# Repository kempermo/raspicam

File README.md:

# raspiCAM

### Setup WiFi
In order to setup WiFi with the correct credentials open the attached file "wpa_supplicant.conf" with a text editor and fill in the correct ssid and password that matches your WiFi setup.

Insert the sd-card from raspi into your computer and open it in the finder. Place the generated "wpa_supplicant.conf" onto the card.

Insert the card back to the raspi and boot. The raspi should now boot and connect to the new WiFi.

### Helpful applications
LanScan for getting the IP address of the raspi - https://apps.apple.com/de/app/lanscan/id472226235?mt=12

### Credetials for login through ssh
User: pi
Passwort: user

### Terminal command for initializing the ssh connection
ssh pi@192.168.20.248 (replace with the proper IP address of your raspi)

### Helpful terminal commands
ls - List current directory contents
cd + ... - entering a directory
cd .. - going back one directory
sudo nano + ... - opening a file in editor
sudo python3 + ... - running a python script with python3
ps aux - list current running processes
sudo kill 425 - kill the process with ID 425

### Helpful key commands
"option"+"c" - quit the current running process

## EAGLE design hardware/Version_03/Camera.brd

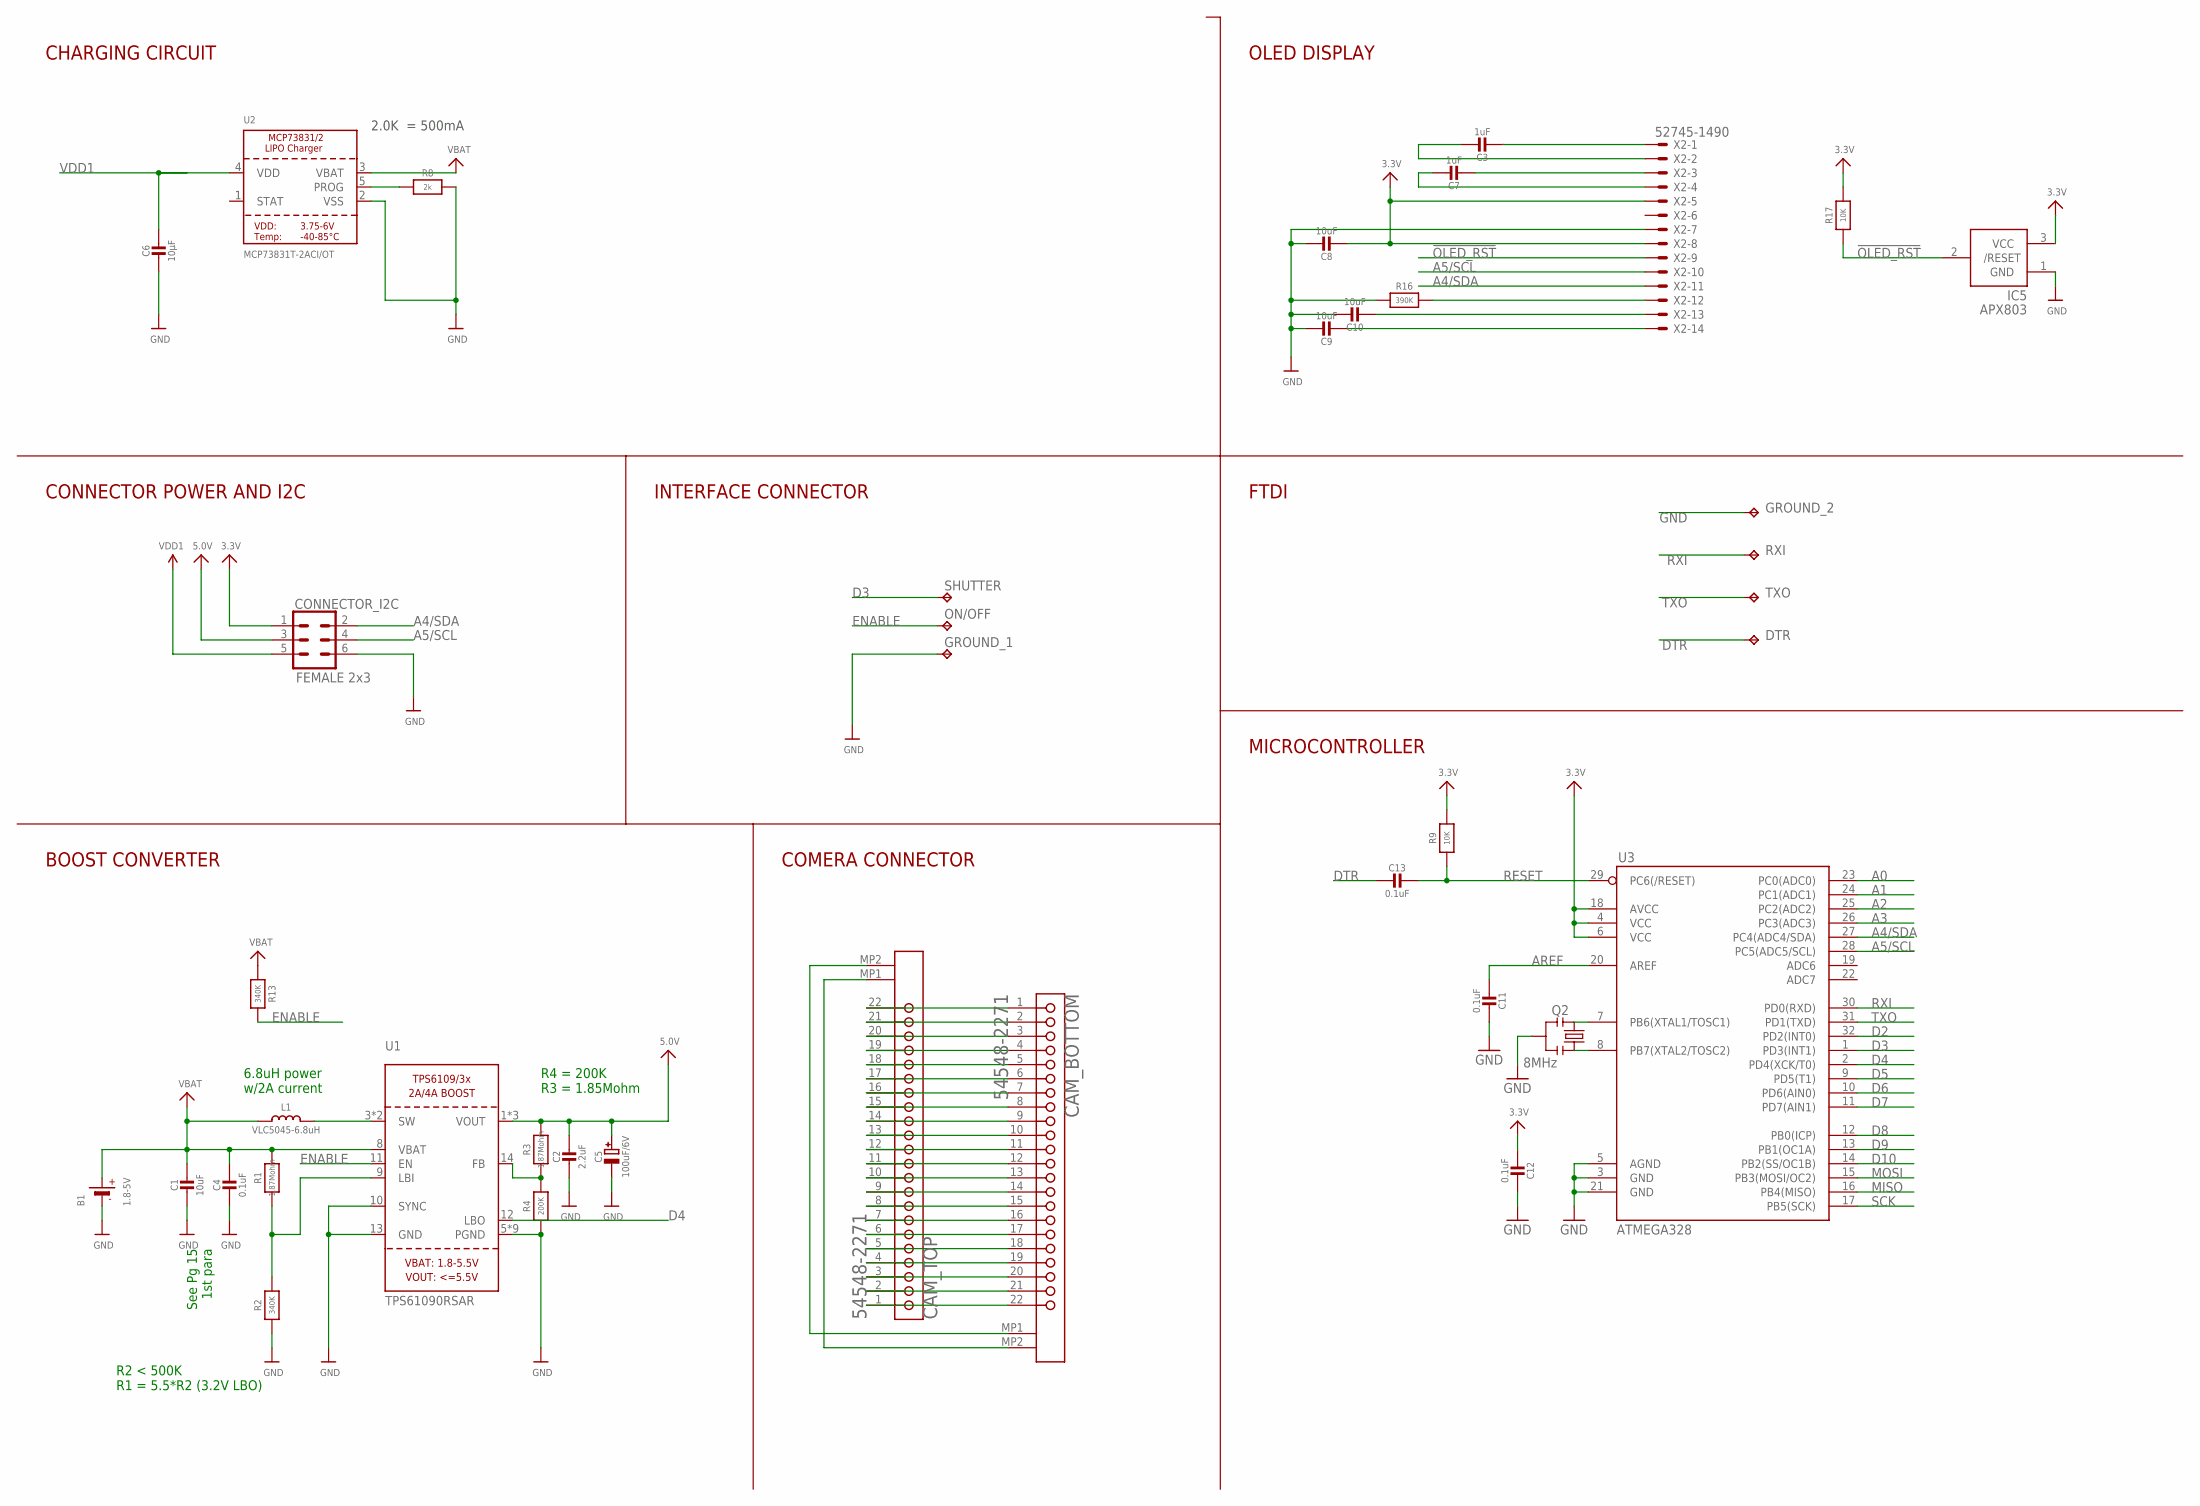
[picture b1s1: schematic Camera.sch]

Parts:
B1: 1.8-5V; JSTPH2
C1, C8, C9, C10: 10uF; 0805-NO
C2: 2.2uF; 0805-NO
C3, C7: 1uF; 0805-NO
C4, C11, C12, C13: 0.1uF; 0805-NO
C5: 100uF/6V; EIA3528-21/B-R
C6: 10µF; 0805-NO
CAM_BOTTOM: MOLEX_54548-2271MOLEX_54548-2271_0_0; MOLEX_54548-2271_0
CAM_TOP: MOLEX_54548-2271MOLEX_54548-2271_0_0; MOLEX_54548-2271_0
CONNECTOR_I2C: FEMALE 2x3; 2X3
DTR: TPB1,27; B1,27
GROUND_1, GROUND_2: TPB1,27; B1,27
IC5: APX803; SOT23
L1: VLC5045-6.8uH; INDUCTOR_5X5MM_TDK_VLC5045
ON/OFF: TPB1,27; B1,27
Q2: 8MHz; RESONATOR-SMD
R1, R3: 1.87Mohm; 0805-NO
R2, R13: 340K; 0805-NO
R4: 200K; 0805-NO
R8: 2k; 0805-NO
R9, R17: 10K; 0805-NO
R16: 390K; 0805-NO
RXI: TPB1,27; B1,27
SHUTTER: TPB1,27; B1,27
TXO: TPB1,27; B1,27
U1: TPS61090RSAR; PVQFN-16
U2: MCP73831T-2ACI/OT; SOT23-5
U3: ATMEGA328; TQFP32-08
X2: 52745-1490

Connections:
3.3V: C8.2, C12.2, CONNECTOR_I2C.1, IC5.3 (VCC), R9.2, R17.2, U3.4 (VCC), U3.6 (VCC), U3.18 (AVCC), X2.5, X2.8
5.0V: C2.1, C5.+, CONNECTOR_I2C.3, R3.2, U1.1 (VOUT), U1.15 (VOUT), U1.16 (VOUT)
!OLED_RST: IC5.2 (/RESET), R17.1, X2.9
A0: U3.23 (PC0(ADC0))
A1: U3.24 (PC1(ADC1))
A2: U3.25 (PC2(ADC2))
A3: U3.26 (PC3(ADC3))
A4/SDA: CONNECTOR_I2C.2, U3.27 (PC4(ADC4/SDA)), X2.11
A5/SCL: CONNECTOR_I2C.4, U3.28 (PC5(ADC5/SCL)), X2.10
AREF: C11.2, U3.20 (AREF)
D2: U3.32 (PD2(INT0))
D3: SHUTTER.TP, U3.1 (PD3(INT1))
D4: U1.12 (LBO), U3.2 (PD4(XCK/T0))
D5: U3.9 (PD5(T1))
D6: U3.10 (PD6(AIN0))
D7: U3.11 (PD7(AIN1))
D8: U3.12 (PB0(ICP))
D9: U3.13 (PB1(OC1A))
D10: U3.14 (PB2(SS/OC1B))
DTR: C13.2, DTR.TP
ENABLE: ON/OFF.TP, R13.2, U1.11 (EN)
GND: B1.1 (-), C1.2, C2.2, C4.2, C5.-, C6.2, C8.1, C9.1, C10.1, C11.1, C12.1, CONNECTOR_I2C.6, GROUND_1.TP, GROUND_2.TP, IC5.1 (GND), Q2.2, R2.1, R4.1, R8.2, R16.1, U1.5 (PGND), U1.6 (PGND), U1.7 (PGND), U1.10 (SYNC), U1.13 (GND), U1.P$18 (PGND), U1.P$19 (PGND), U1.P$20 (PGND), U1.P$21 (PGND), U1.P$22 (PGND), U1.THERMAL (PGND), U2.2 (VSS), U3.3 (GND), U3.5 (AGND), U3.21 (GND), X2.7
MISO: U3.16 (PB4(MISO))
MOSI: U3.15 (PB3(MOSI/OC2))
unnamed: L1.P$2 (2), U1.3 (SW), U1.4 (SW)
unnamed: CAM_BOTTOM.MP1, CAM_TOP.MP2
unnamed: R1.1, R2.2, U1.9 (LBI)
unnamed: CAM_BOTTOM.MP2, CAM_TOP.MP1
unnamed: R3.1, R4.2, U1.14 (FB)
unnamed: CAM_BOTTOM.1, CAM_TOP.22
unnamed: CAM_BOTTOM.2, CAM_TOP.21
unnamed: R8.1, U2.5 (PROG)
unnamed: CAM_BOTTOM.3, CAM_TOP.20
unnamed: CAM_BOTTOM.4, CAM_TOP.19
unnamed: C3.2, X2.1
unnamed: C3.1, X2.2
unnamed: C7.2, X2.3
unnamed: C7.1, X2.4
unnamed: C10.2, X2.13
unnamed: R16.2, X2.12
unnamed: C9.2, X2.14
unnamed: Q2.1, U3.8 (PB7(XTAL2/TOSC2))
unnamed: Q2.3, U3.7 (PB6(XTAL1/TOSC1))
unnamed: CAM_BOTTOM.5, CAM_TOP.18
unnamed: CAM_BOTTOM.6, CAM_TOP.17
unnamed: CAM_BOTTOM.7, CAM_TOP.16
unnamed: CAM_BOTTOM.8, CAM_TOP.15
unnamed: CAM_BOTTOM.9, CAM_TOP.14
unnamed: CAM_BOTTOM.10, CAM_TOP.13
unnamed: CAM_BOTTOM.11, CAM_TOP.12
unnamed: CAM_BOTTOM.12, CAM_TOP.11
unnamed: CAM_BOTTOM.13, CAM_TOP.10
unnamed: CAM_BOTTOM.14, CAM_TOP.9
unnamed: CAM_BOTTOM.15, CAM_TOP.8
unnamed: CAM_BOTTOM.16, CAM_TOP.7
unnamed: CAM_BOTTOM.17, CAM_TOP.6
unnamed: CAM_BOTTOM.18, CAM_TOP.5
unnamed: CAM_BOTTOM.19, CAM_TOP.4
unnamed: CAM_BOTTOM.20, CAM_TOP.3
unnamed: CAM_BOTTOM.21, CAM_TOP.2
unnamed: CAM_BOTTOM.22, CAM_TOP.1
RESET: C13.1, R9.1, U3.29 (PC6(/RESET))
RXI: RXI.TP, U3.30 (PD0(RXD))
SCK: U3.17 (PB5(SCK))
TXO: TXO.TP, U3.31 (PD1(TXD))
VBAT: B1.2 (+), C1.1, C4.1, L1.P$1 (1), R1.2, R13.1, U1.8 (VBAT), U2.3 (VBAT)
VDD1: C6.1, CONNECTOR_I2C.5, U2.4 (VDD)

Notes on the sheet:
See Pg 15 1st para
6.8uH power w/2A current
R2 < 500K R1 = 5.5*R2 (3.2V LBO)
R4 = 200K R3 = 1.85Mohm
2.0K = 500mA
CHARGING CIRCUIT
CONNECTOR POWER AND I2C
INTERFACE CONNECTOR
BOOST CONVERTER
MICROCONTROLLER
OLED DISPLAY
COMERA CONNECTOR
FTDI

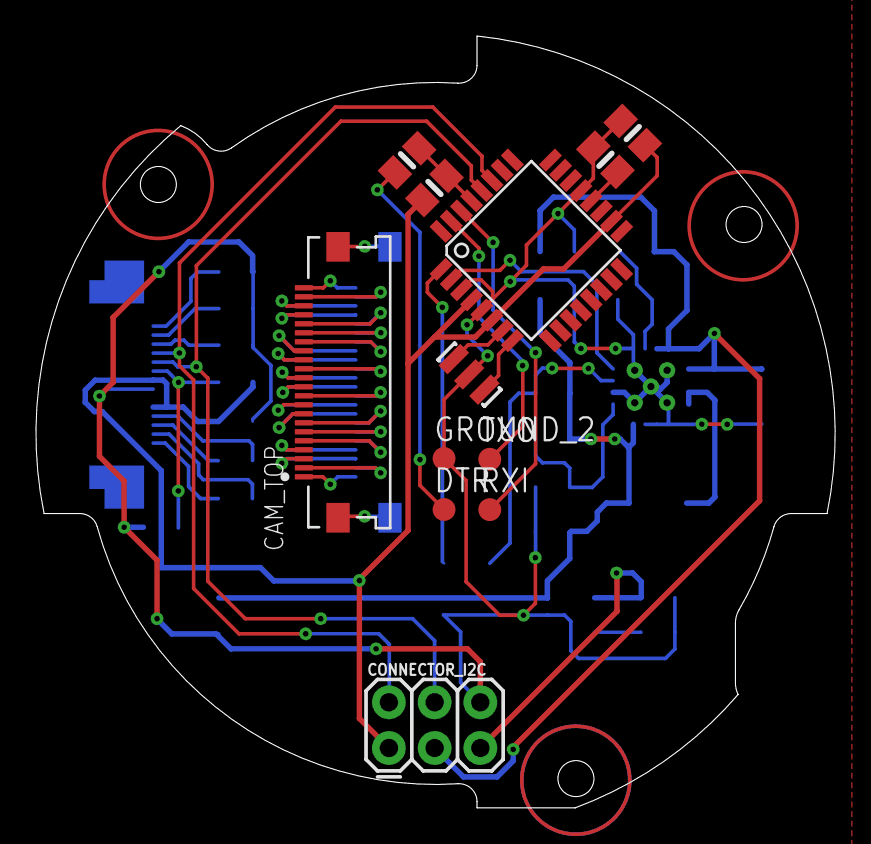
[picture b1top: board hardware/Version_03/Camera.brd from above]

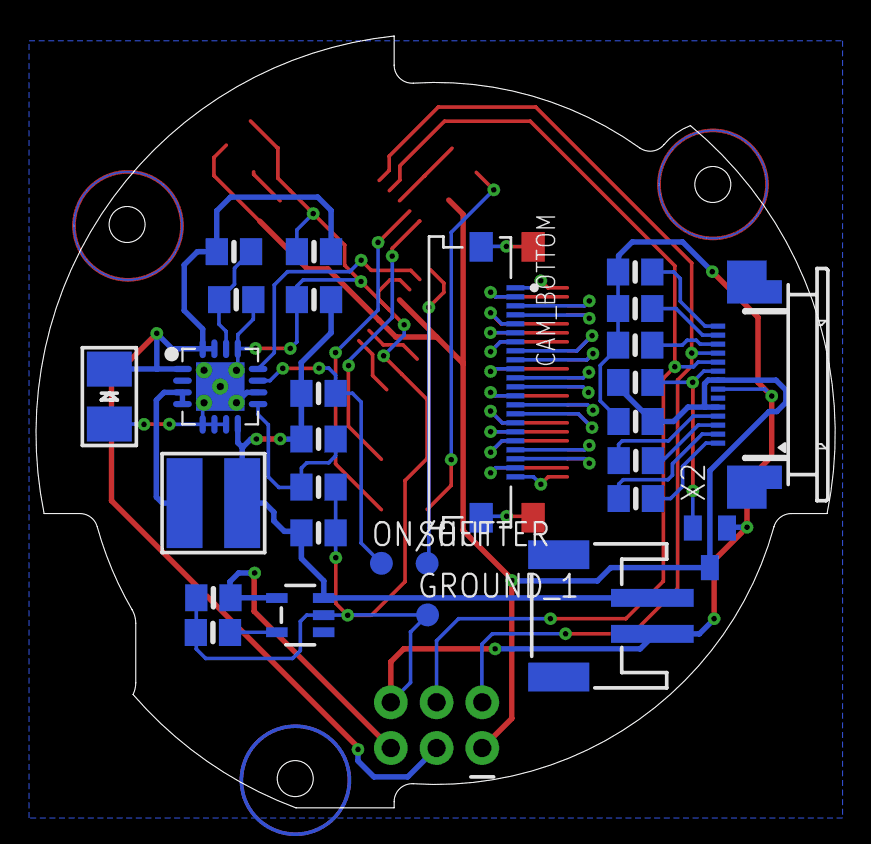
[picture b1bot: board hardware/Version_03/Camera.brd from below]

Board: 2 copper layers, 44.4 x 42.9 mm, 40 parts (28 on the bottom side), 53 nets.

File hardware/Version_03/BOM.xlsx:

Check | Qty | Part | Value | Type | URL
 | 5 | C1,C6,C8,C9,C10 | 10uF | Cap | https://www.mouser.de/ProductDetail/KEMET/C0805C106M8PACTU?q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
 | 1 | C2 | 2.2uF | Cap
 | 2 | C3,C7 | 1uF | Cap | https://www.mouser.de/ProductDetail/KEMET/C0805C105K8RACTU?q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
 | 4 | C4,C11,C12,C13 | 0.1uF | Cap
 | 1 | C5 | 100uF | Cap
 | 2 | R1,R3 | 1.87mOhm | Res
 | 2 | R2,R13 | 340kOhm | Res
 | 1 | R4 | 200kOhm | Res
 | 1 | R8 | 2kOhm | Res
 | 2 | R9,R17 | 10kOhm | Res
 | 1 | R16 | 390kOhm | Res
 | 1 | U1 | TPS61090RSAR | Vreg | https://www.mouser.de/ProductDetail/Texas-Instruments/TPS610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
 | 1 | U2 | MCP73831T | Charge Controler
 | 1 | U3 | ATMEGA328 | Microcontroller | https://www.mouser.de/ProductDetail/Microchip-Technology/ATM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
 | 1 | L1 | VLC5045-6.8uH | Inductor
 | 1 | IC5 | ﻿APX803 | Transistor
 | 2 | CAM_BOTTOM, CAM_TOP | MOLEX_54548-2271MOLEX_54548-2271_0_0
 | 1 | Q2 | 8Mhz | Resonator
 | 2 |  | 54548-1472 | Connector | https://www.mouser.de/ProductDetail/Molex/54548-1472?qs=vvQt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

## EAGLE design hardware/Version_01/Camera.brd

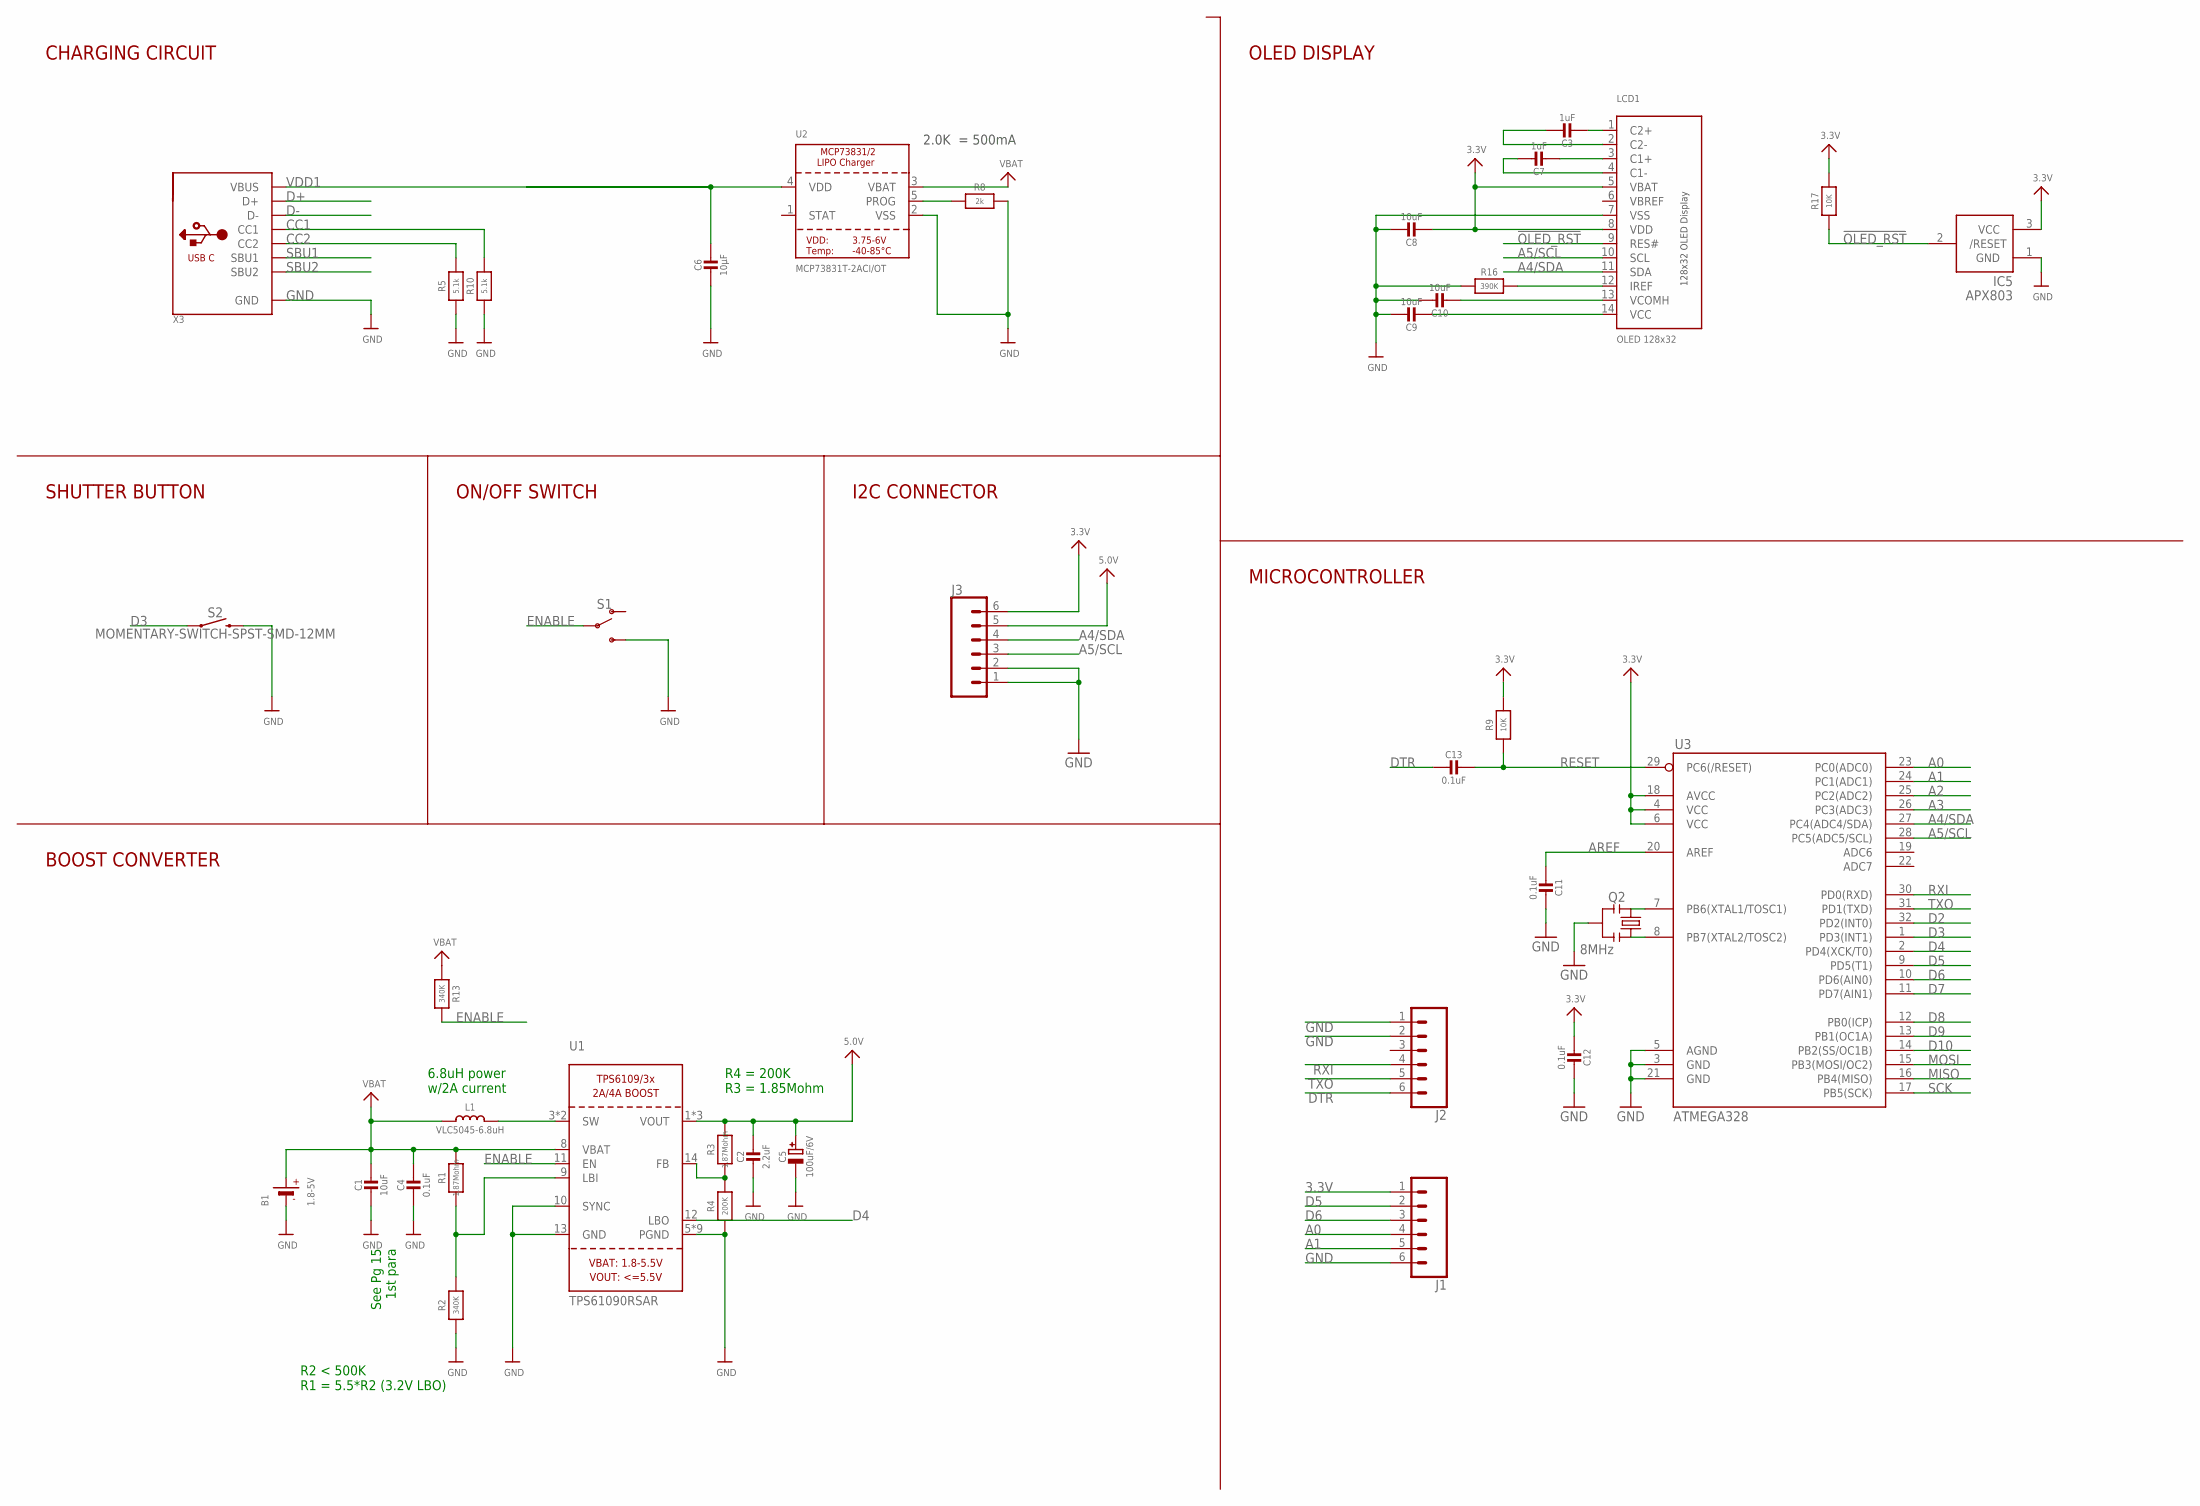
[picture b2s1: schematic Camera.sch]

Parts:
B1: 1.8-5V; JSTPH2
C1, C8, C9, C10: 10uF; 0805-NO
C2: 2.2uF; 0805-NO
C3, C7: 1uF; 0805-NO
C4, C11, C12, C13: 0.1uF; 0805-NO
C5: 100uF/6V; EIA3528-21/B-R
C6: 10µF; 0805-NO
IC5: APX803; SOT23
J1, J2, J3: CONN_06SMD-FEMALE-V2; 1X06-SMD-FEMALE
L1: VLC5045-6.8uH; INDUCTOR_5X5MM_TDK_VLC5045
LCD1: OLED 128x32; UG-2832HSWEG02_WRAPUNDER
Q2: 8MHz; RESONATOR-SMD
R1, R3: 1.87Mohm; 0805-NO
R2, R13: 340K; 0805-NO
R4: 200K; 0805-NO
R5, R10: 5.1k; 0805-NO
R8: 2k; 0805-NO
R9, R17: 10K; 0805-NO
R16: 390K; 0805-NO
S1: SWITCH-SPDT-SMD-RIGHT-ANGLE; SWITCH_SPST_SMD_A
S2: MOMENTARY-SWITCH-SPST-SMD-12MM; TACTILE_SWITCH_SMD_12MM
U1: TPS61090RSAR; PVQFN-16
U2: MCP73831T-2ACI/OT; SOT23-5
U3: ATMEGA328; TQFP32-08
X3: USB_C; USB_C_CUSB31-CFM2AX-01-X

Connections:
3.3V: C8.2, C12.2, IC5.3 (VCC), J1.1, J3.6, LCD1.5 (VBAT), LCD1.8 (VDD), R9.2, R17.2, U3.4 (VCC), U3.6 (VCC), U3.18 (AVCC)
5.0V: C2.1, C5.+, J3.5, R3.2, U1.1 (VOUT), U1.15 (VOUT), U1.16 (VOUT)
!OLED_RST: IC5.2 (/RESET), LCD1.9 (RES#), R17.1
A0: J1.4, U3.23 (PC0(ADC0))
A1: J1.5, U3.24 (PC1(ADC1))
A2: U3.25 (PC2(ADC2))
A3: U3.26 (PC3(ADC3))
A4/SDA: J3.4, LCD1.11 (SDA), U3.27 (PC4(ADC4/SDA))
A5/SCL: J3.3, LCD1.10 (SCL), U3.28 (PC5(ADC5/SCL))
AREF: C11.2, U3.20 (AREF)
CC1: R10.2, X3.A5 (CC1)
CC2: R5.2, X3.B5 (CC2)
D2: U3.32 (PD2(INT0))
D3: S2.1, U3.1 (PD3(INT1))
D4: U1.12 (LBO), U3.2 (PD4(XCK/T0))
D5: J1.2, U3.9 (PD5(T1))
D6: J1.3, U3.10 (PD6(AIN0))
D7: U3.11 (PD7(AIN1))
D8: U3.12 (PB0(ICP))
D9: U3.13 (PB1(OC1A))
D10: U3.14 (PB2(SS/OC1B))
D+: X3.A6 (D+), X3.B6 (D+)
D-: X3.A7 (D-), X3.B7 (D-)
DTR: C13.2, J2.6
ENABLE: R13.2, S1.2, U1.11 (EN)
GND: B1.1 (-), C1.2, C2.2, C4.2, C5.-, C6.2, C8.1, C9.1, C10.1, C11.1, C12.1, IC5.1 (GND), J1.6, J2.1, J2.2, J3.1, J3.2, LCD1.7 (VSS), Q2.2, R2.1, R4.1, R5.1, R8.2, R10.1, R16.1, S1.3 (S), S2.3 (2), U1.5 (PGND), U1.6 (PGND), U1.7 (PGND), U1.10 (SYNC), U1.13 (GND), U1.P$18 (PGND), U1.P$19 (PGND), U1.P$20 (PGND), U1.P$21 (PGND), U1.P$22 (PGND), U1.THERMAL (PGND), U2.2 (VSS), U3.3 (GND), U3.5 (AGND), U3.21 (GND), X3.A1B12 (GND), X3.B1A12 (GND)
MISO: U3.16 (PB4(MISO))
MOSI: U3.15 (PB3(MOSI/OC2))
unnamed: L1.P$2 (2), U1.3 (SW), U1.4 (SW)
unnamed: R1.1, R2.2, U1.9 (LBI)
unnamed: R3.1, R4.2, U1.14 (FB)
unnamed: R8.1, U2.5 (PROG)
unnamed: C3.2, LCD1.1 (C2+)
unnamed: C3.1, LCD1.2 (C2-)
unnamed: C7.2, LCD1.3 (C1+)
unnamed: C7.1, LCD1.4 (C1-)
unnamed: C10.2, LCD1.13 (VCOMH)
unnamed: LCD1.12 (IREF), R16.2
unnamed: C9.2, LCD1.14 (VCC)
unnamed: Q2.1, U3.8 (PB7(XTAL2/TOSC2))
unnamed: Q2.3, U3.7 (PB6(XTAL1/TOSC1))
RESET: C13.1, R9.1, U3.29 (PC6(/RESET))
RXI: J2.4, U3.30 (PD0(RXD))
SBU1: X3.A8 (SBU1)
SBU2: X3.B8 (SBU2)
SCK: U3.17 (PB5(SCK))
TXO: J2.5, U3.31 (PD1(TXD))
VBAT: B1.2 (+), C1.1, C4.1, L1.P$1 (1), R1.2, R13.1, U1.8 (VBAT), U2.3 (VBAT)
VBREF: LCD1.6 (VBREF)
VDD1: C6.1, U2.4 (VDD), X3.A4B9 (VBUS), X3.B4A9 (VBUS)

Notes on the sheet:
See Pg 15 1st para
6.8uH power w/2A current
R2 < 500K R1 = 5.5*R2 (3.2V LBO)
R4 = 200K R3 = 1.85Mohm
2.0K = 500mA
CHARGING CIRCUIT
SHUTTER BUTTON
ON/OFF SWITCH
I2C CONNECTOR
BOOST CONVERTER
MICROCONTROLLER
OLED DISPLAY

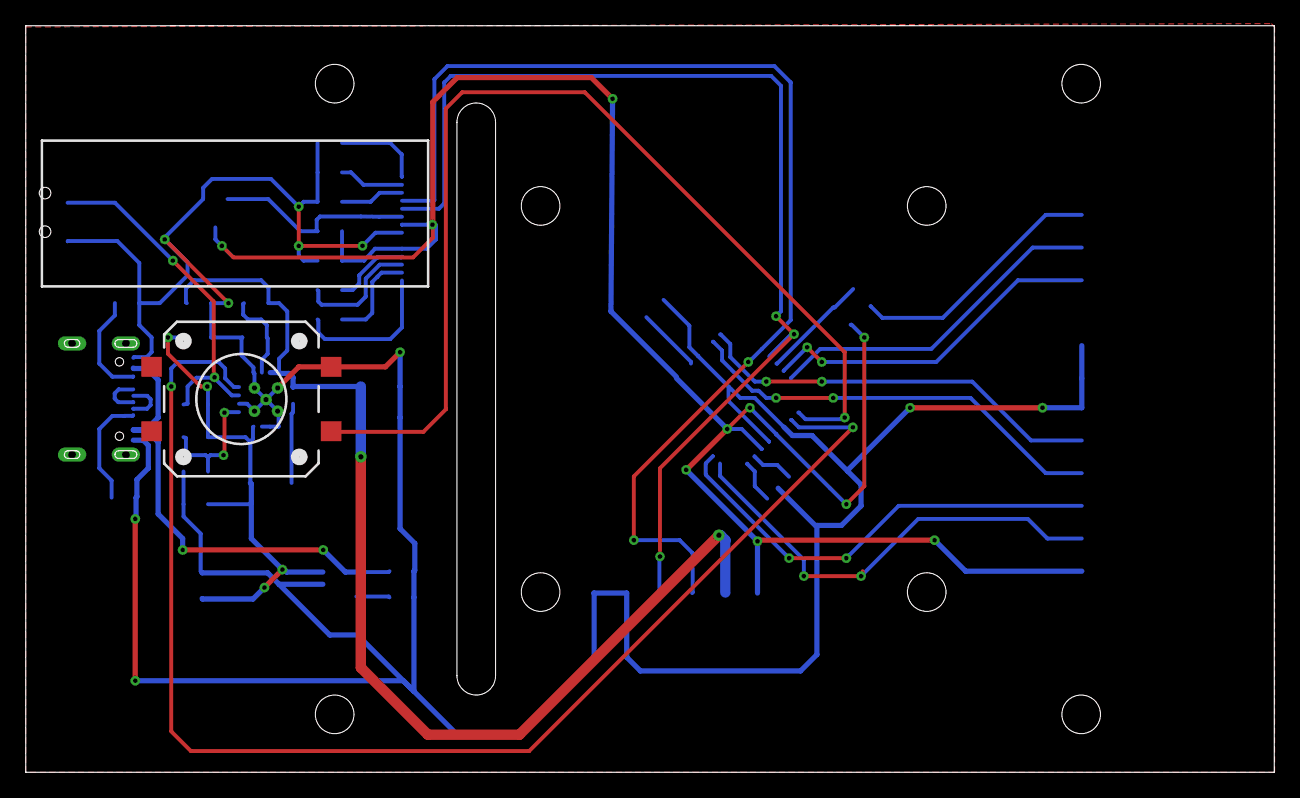
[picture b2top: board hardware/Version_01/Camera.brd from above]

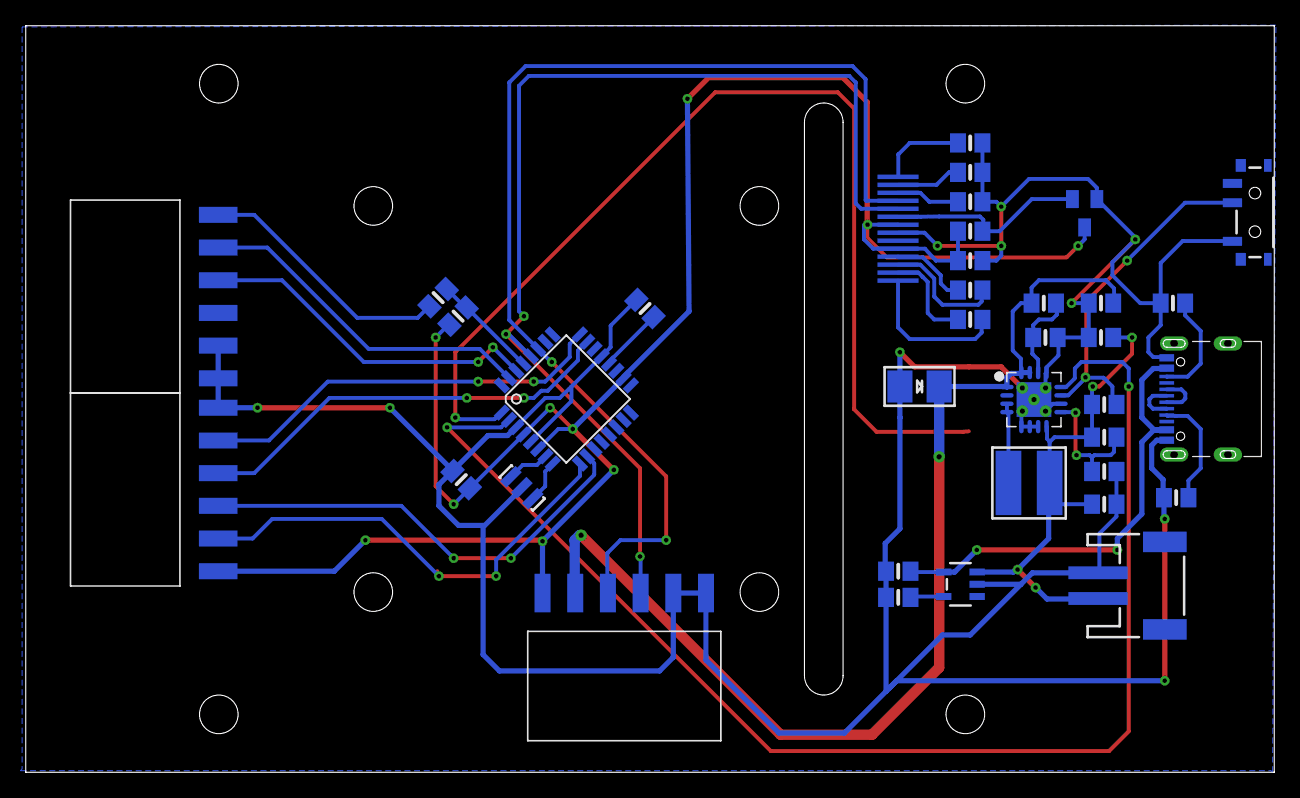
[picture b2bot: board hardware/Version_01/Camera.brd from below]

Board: 2 copper layers, 97.0 x 58.0 mm, 39 parts (36 on the bottom side), 37 nets.

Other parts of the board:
U$9: PHOENIX_LOGO

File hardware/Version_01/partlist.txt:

Partlist

Exported from Camera.sch at 05.01.21 22:15

EAGLE Version 9.6.2 Copyright (c) 1988-2020 Autodesk, Inc.

Assembly variant: 

Part     		Value                          Device                         Package                    Library             Sheet

B1       		1.8-5V                         BATTERY                        JSTPH2                     microbuilder        1

C2       		2.2uF                          CAP_CERAMIC0805-NOOUTLINE      0805-NO                    microbuilder        1
C3+C7      		1uF                            CAP_CERAMIC0805-NOOUTLINE      0805-NO                    microbuilder        1
C5       		100uF/6V                       CAP_TANTALUMB/3528_REFLOW      EIA3528-21/B-R             microbuilder        1
C1+C6+C8+C9+C10       	10uF                           CAP_CERAMIC0805-NOOUTLINE      0805-NO                    microbuilder        1
C4+C11+C12+C13      	0.1uF                          CAP_CERAMIC0805-NOOUTLINE      0805-NO                    microbuilder        1

IC5      		APX803                         AXP083-SAG                     SOT23                      adafruit            1

J1                                      	       CONN_06SMD-FEMALE-V2           1X06-SMD-FEMALE            SparkFun-Connectors 1
J2                                      	       CONN_06SMD-FEMALE-V2           1X06-SMD-FEMALE            SparkFun-Connectors 1
J3                                      	       CONN_06SMD-FEMALE-V2           1X06-SMD-FEMALE            SparkFun-Connectors 1

L1       		VLC5045-6.8uH                  INDUCTORTDK_VLC5045            INDUCTOR_5X5MM_TDK_VLC5045 microbuilder        1
LCD1     		OLED 128x32                    DISP_OLED_UG-2832HSWEG02       UG-2832HSWEG02_WRAPUNDER   microbuilder        1
Q2       		8MHz                           RESONATORSMD                   RESONATOR-SMD              SparkFun            1

R1+R3       		1.87Mohm                       RESISTOR0805_NOOUTLINE         0805-NO                    microbuilder        1
R4       		200K                           RESISTOR0805_NOOUTLINE         0805-NO                    microbuilder        1
R8       		2k                             RESISTOR0805_NOOUTLINE         0805-NO                    microbuilder        1
R9+R17   		10K                            RESISTOR0805_NOOUTLINE         0805-NO                    microbuilder        1
R5+R10   		5.1k                           RESISTOR0805_NOOUTLINE         0805-NO                    microbuilder        1
R2+R13      		340K                           RESISTOR0805_NOOUTLINE         0805-NO                    microbuilder        1
R16      		390K                           RESISTOR0805_NOOUTLINE         0805-NO                    microbuilder        1

S1                      SWITCH-SPDT-SMD-RIGHT-ANGLE    SWITCH_SPST_SMD_A          				 SparkFun-Switches   1
S2       		MOMENTARY-SWITCH-SPST-SMD-12MM MOMENTARY-SWITCH-SPST-SMD-12MM TACTILE_SWITCH_SMD_12MM    SparkFun-Switches   1
U1       		TPS61090RSAR                   VREG_TPS6103X                  PVQFN-16                   microbuilder        1
U2       		MCP73831T-2ACI/OT              MCP73831/2                     SOT23-5                    microbuilder        1
U3       		ATMEGA328                      ATMEGA168                      TQFP32-08                  SparkFun            1
X3                          			       USB_C                          USB_C_CUSB31-CFM2AX-01-X   microbuilder        1

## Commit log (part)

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2021-03-15 included wpa_supplicant.conf
2021-03-15 Added hardware and software files
2022-03-10 Updated schematic
2022-03-11 Updated the schematic
2024-04-23 Latest version
2025-10-20 Latest Version V03
2025-10-20 Added Arduino file
2025-10-21 Version 3 for production
2026-02-15 Update
    Update
2026-02-23 Working version

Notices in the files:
parts and their libraries:
microbuilder: This work is placed in the public domain, and may be freely used for commercial and non-commercial work with the following conditions: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
SparkFun-Connectors: Licensing: Creative Commons ShareAlike 4.0 International - https://creativecommons.org/licenses/by-sa/4.0
